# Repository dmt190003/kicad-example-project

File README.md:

# KIDCAD Intro PCB Project

Hello,

This is the initial project

Cheers man

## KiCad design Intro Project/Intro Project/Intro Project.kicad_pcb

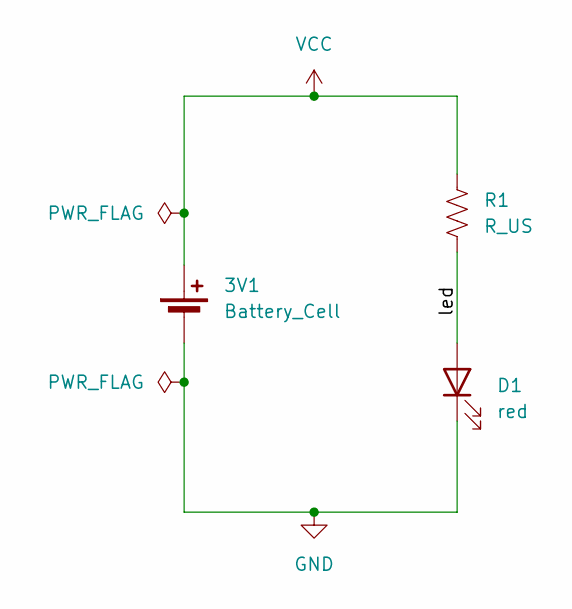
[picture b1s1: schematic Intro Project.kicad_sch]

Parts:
3V1: Battery_Cell; BatteryHolder_Keystone_1058_1x2032
D1: red; LED_D5.0mm
R1: R_US; R_Axial_DIN0309_L9.0mm_D3.2mm_P12.70mm_Horizontal

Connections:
/led: D1.2 (A), R1.2
GND: 3V1.2 (-), D1.1 (K)
VCC: 3V1.1 (+), R1.1

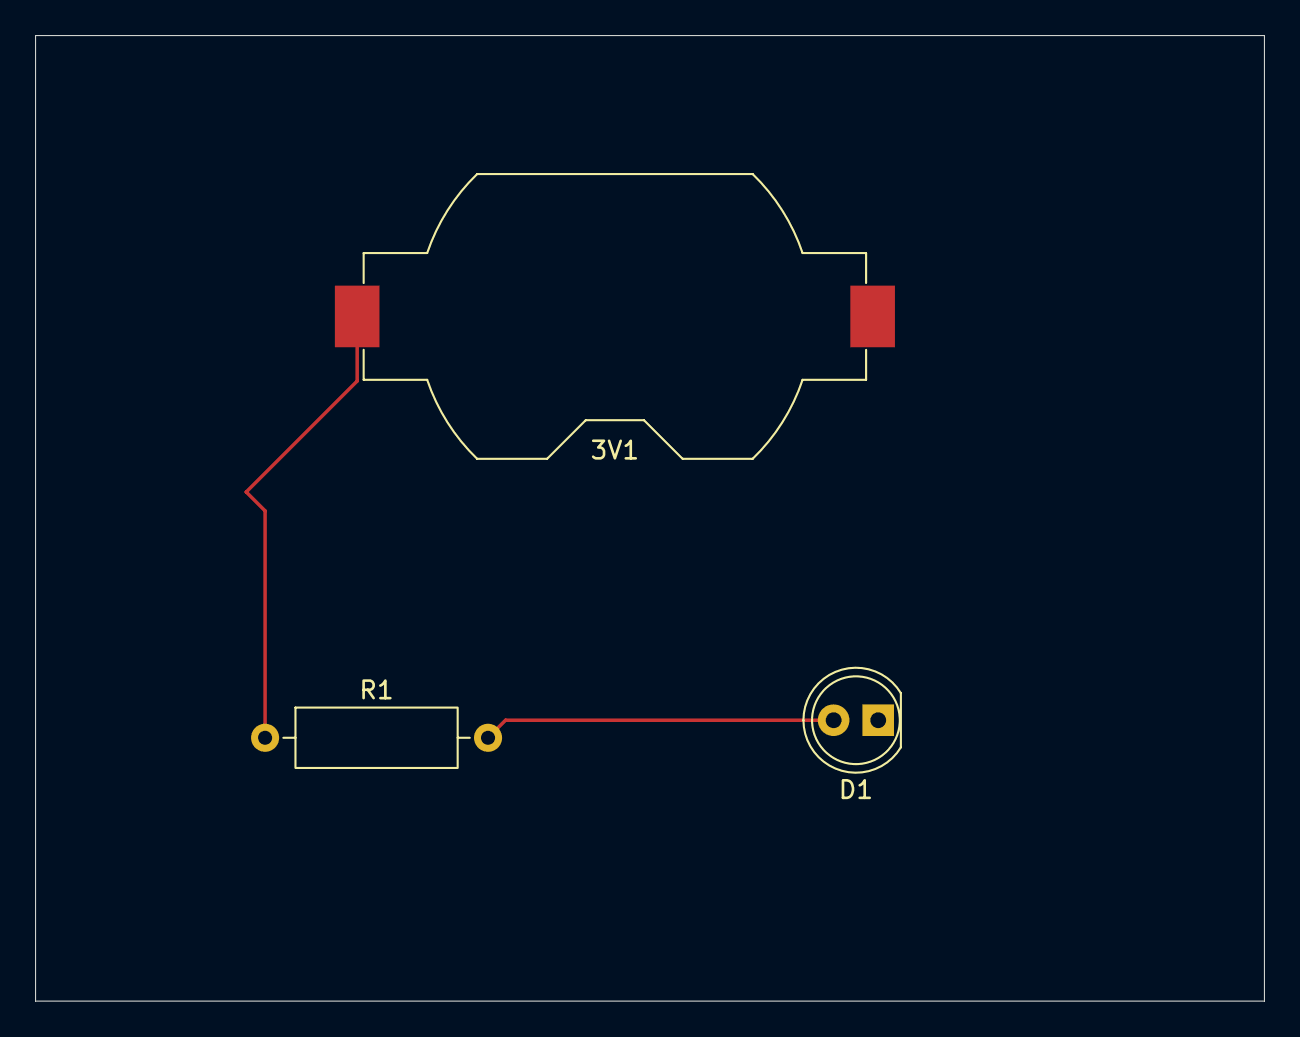
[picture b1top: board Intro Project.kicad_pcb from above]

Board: 2 copper layers, 70.0 x 55.0 mm, 3 parts (0 on the bottom side), 3 nets.

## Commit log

2026-04-01 Initial upload
